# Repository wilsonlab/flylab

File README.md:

## 9.17 Revamp
Materials, designs, and tools for retrofitting 9.17 course with modern, open-source ephys equipment.

### BOM

See this google doc:

https://docs.google.com/spreadsheets/d/1sXGyNVC1GGGA84c10rlup0MCN_12TPQaVe6azXBhNLY/edit#gid=0

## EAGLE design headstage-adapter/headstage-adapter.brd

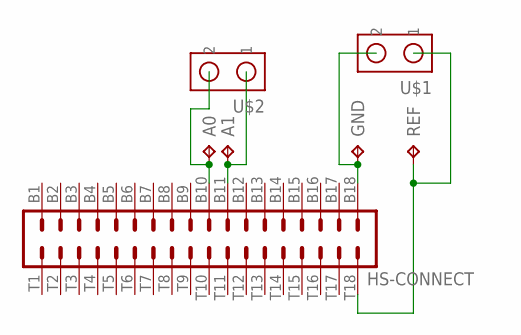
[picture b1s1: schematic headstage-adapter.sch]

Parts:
A0, A1: 220-S02-100; AMPHENOL-220
GND: 220-S02-100; AMPHENOL-220
HS-CONNECT: NPD-AA-36; OMNETICS_NPD-AA-36-GS
REF: 220-S02-100; AMPHENOL-220
U$1, U$2: SCREW2

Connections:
GND: GND.TP, HS-CONNECT.B18, U$1.P$2 (2)
unnamed: A0.TP, HS-CONNECT.B10, U$2.P$2 (2)
unnamed: A1.TP, HS-CONNECT.B11, U$2.P$1 (1)
unnamed: HS-CONNECT.T18, REF.TP, U$1.P$1 (1)

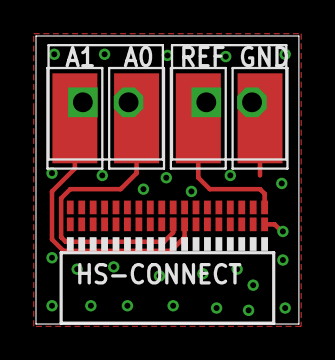
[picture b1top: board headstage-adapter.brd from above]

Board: 2 copper layers, 14.6 x 16.0 mm, 7 parts (0 on the bottom side), 4 nets.

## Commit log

2016-08-05 Added inital CAD files, PCB designs, etc.
2016-08-05 Added headstage gerbers.
2016-11-10 Added example recording configuraiton for the headstage adapter board.
